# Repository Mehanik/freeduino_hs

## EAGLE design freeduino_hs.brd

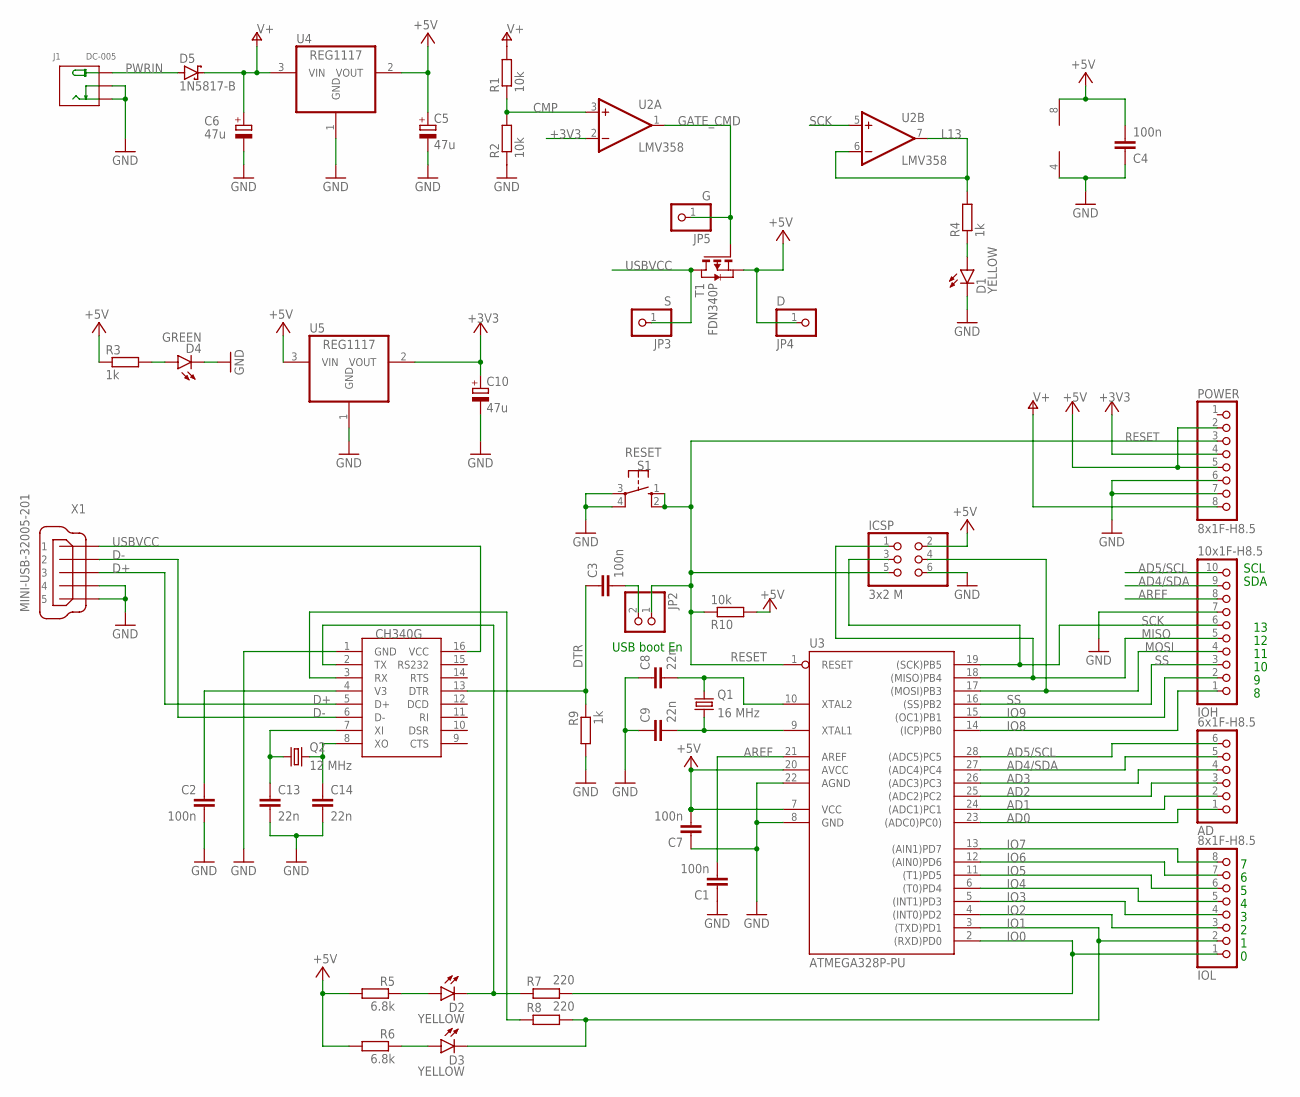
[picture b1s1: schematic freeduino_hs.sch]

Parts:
AD: 6x1F-H8.5; 1X06
C1, C2, C3, C4, C7: 100n; C050-024X044
C5, C6, C10: 47u; E2,5-5
C8, C9, C13, C14: 22n; C050-024X044
D1, D2, D3: YELLOW; LED3MM
D4: GREEN; LED3MM
D5: 1N5817-B; DO41-7.6
ICSP: 3x2 M; 2X03
IOH: 10x1F-H8.5; 1X10
IOL: 8x1F-H8.5; 1X08
J1: DC-005; DCJ3P-14.2X11.0X9.0MM
JP2: PINHD-1X2; 1X02
JP3: S; 1X01
JP4: D; 1X01
JP5: G; 1X01
POWER: 8x1F-H8.5; 1X08
Q1: 16 MHz; HC49/S
Q2: 12 MHz; HC49/S
R1, R2, R10: 10k; 0204/7
R3, R4, R9: 1k; 0204/7
R5, R6: 6.8k; 0204/7
R7, R8: 220; 0204/7
S1: RESET; B3F-10XX
T1: FDN340P; SOT-23
U1: CH340G; SOIC16
U2: LMV358; SO08
U3: ATMEGA328P-PU; DIL28-3
U4, U5: REG1117; SOT223
X1: MINI-USB-32005-201; 32005-201

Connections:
+3V3: C10.+, POWER.4, U2.2 (-IN), U5.2 (VOUT)
+5V: C4.2, C5.+, C7.2, ICSP.2, JP4.1, POWER.2, POWER.5, R3.1, R5.2, R6.2, R10.2, T1.2 (S), U2.8 (V+), U3.7 (VCC), U3.20 (AVCC), U4.2 (VOUT), U5.3 (VIN)
AD0: AD.1, U3.23 ((ADC0)PC0))
AD1: AD.2, U3.24 ((ADC1)PC1)
AD2: AD.3, U3.25 ((ADC2)PC2)
AD3: AD.4, U3.26 ((ADC3)PC3)
AD4/SDA: AD.5, IOH.9, U3.27 ((ADC4)PC4)
AD5/SCL: AD.6, IOH.10, U3.28 ((ADC5)PC5)
AREF: C1.2, IOH.8, U3.21 (AREF)
CMP: R1.1, R2.2, U2.3 (+IN)
D+: U1.5 (D+), X1.3
D-: U1.6 (D-), X1.2
DTR: C3.1, R9.1, U1.13 (DTR)
GATE_CMD: JP5.1, T1.3 (G), U2.1 (OUT)
GND: C1.1, C2.2, C4.1, C5.-, C6.-, C7.1, C8.1, C9.1, C10.-, C13.2, C14.2, D1.K (C), D4.K (C), ICSP.6, IOH.7, J1.-1 (-), J1.-2 (CDN), POWER.6, POWER.7, R2.1, R9.2, S1.3, S1.4 (P1), U1.1 (GND), U2.4 (V-), U3.8 (GND), U3.22 (AGND), U4.1 (GND), U5.1 (GND), X1.4, X1.5
IO0: IOL.1, R7.2, U3.2 ((RXD)PD0)
IO1: D3.K (C), IOL.2, R8.2, U3.3 ((TXD)PD1)
IO2: IOL.3, U3.4 ((INT0)PD2)
IO3: IOL.4, U3.5 ((INT1)PD3)
IO4: IOL.5, U3.6 ((T0)PD4)
IO5: IOL.6, U3.11 ((T1)PD5)
IO6: IOL.7, U3.12 ((AIN0)PD6)
IO7: IOL.8, U3.13 ((AIN1)PD7)
IO8: IOH.1, U3.14 ((ICP)PB0)
IO9: IOH.2, U3.15 ((OC1)PB1)
L13: R4.2, U2.6 (-IN), U2.7 (OUT)
M8RXD: R8.1, U1.3 (RX)
MISO: ICSP.1, IOH.5, U3.18 ((MISO)PB4)
MOSI: ICSP.4, IOH.4, U3.17 ((MOSI)PB3)
unnamed: D1.A, R4.1
unnamed: C2.1, U1.4 (V3)
unnamed: D4.A, R3.2
unnamed: C3.2, JP2.2
unnamed: D3.A, R6.1
unnamed: D2.A, R5.1
unnamed: D2.K (C), R7.1, U1.2 (TX)
PWRIN: D5.A, J1.+
RESET: ICSP.5, JP2.1, POWER.3, R10.1, S1.1 (S), S1.2 (S1), U3.1 (RESET)
SCK: ICSP.3, IOH.6, U2.5 (+IN), U3.19 ((SCK)PB5)
SS: IOH.3, U3.16 ((SS)PB2)
USBVCC: JP3.1, T1.1 (D), U1.16 (VCC), X1.1
V+: C6.+, D5.C, POWER.8, R1.2, U4.3 (VIN)
XI: C13.1, Q2.2, U1.7 (XI)
XO: C14.1, Q2.1, U1.8 (XO)
XTAL1: C9.2, Q1.1, U3.9 (XTAL1)
XTAL2: C8.2, Q1.2, U3.10 (XTAL2)

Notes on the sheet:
USB boot En
SDA
SCL

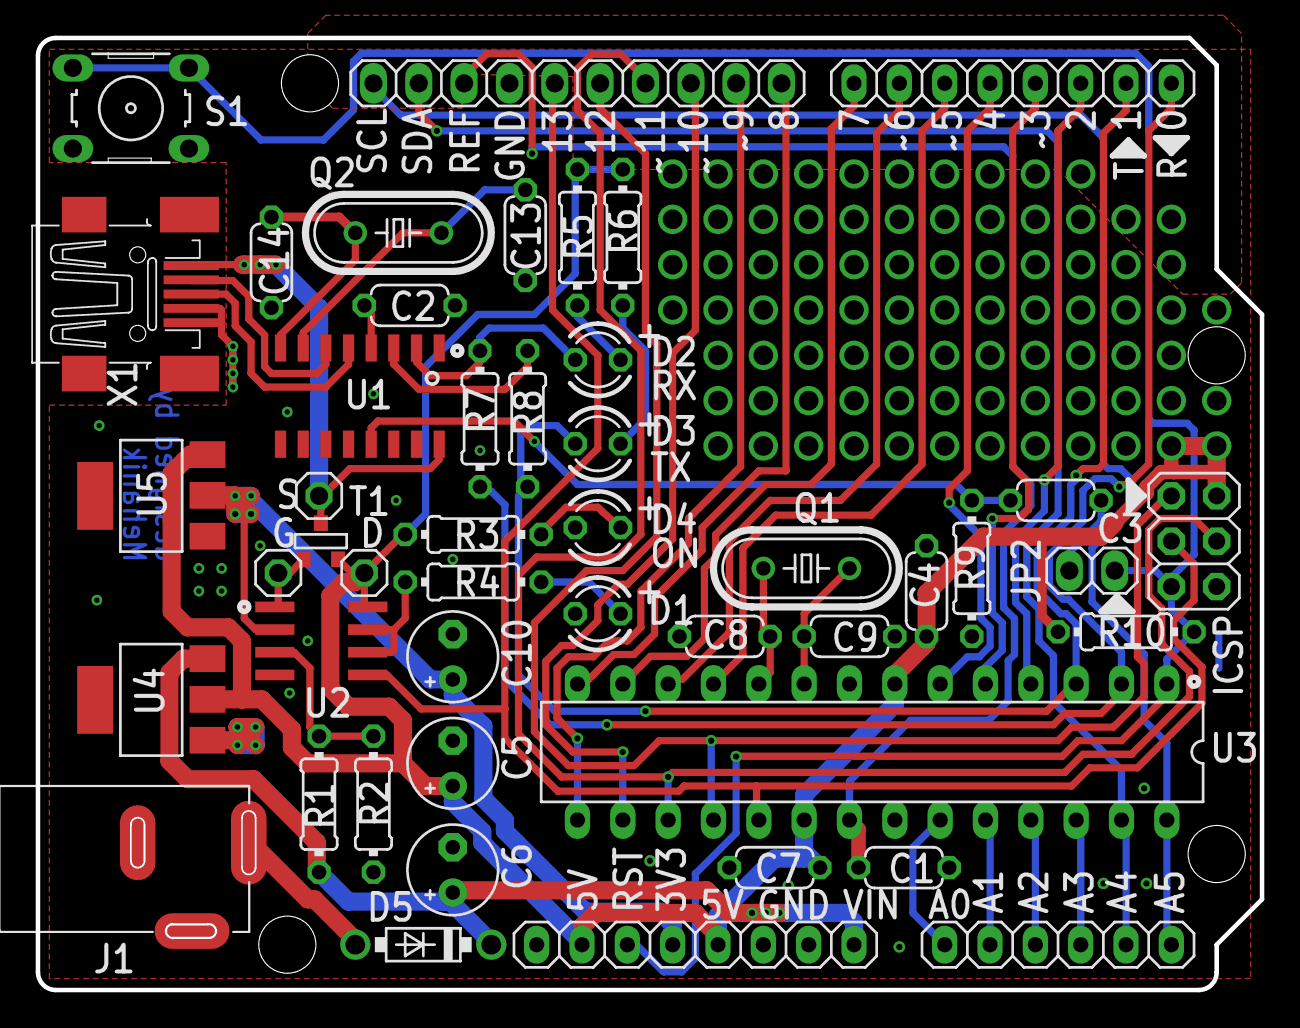
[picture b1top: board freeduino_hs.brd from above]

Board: 2 copper layers, 68.6 x 53.3 mm, 47 parts (0 on the bottom side), 46 nets.

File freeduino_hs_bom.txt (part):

Partlist exported from /home/eugene/eagle/Freeduiono/HS/freeduino_hs.sch at 14.02.17 21:21

Part  Value                Device                        Package               Description                                       MF MPN      OC_FARNELL OC_NEWARK VALUE 
AD    6x1F-H8.5            PINHD-1X6                     1X06                  PIN HEADER                                                                               
C1    100n                 C-EU050-024X044               C050-024X044          CAPACITOR, European symbol                                                               
C2    100n                 C-EU050-024X044               C050-024X044          CAPACITOR, European symbol                                                               
C3    100n                 C-EU050-024X044               C050-024X044          CAPACITOR, European symbol                                                               
C4    100n                 C-EU050-024X044               C050-024X044          CAPACITOR, European symbol                                                               
C5    47u                  CPOL-EUE2.5-5                 E2,5-5                POLARIZED CAPACITOR, European symbol                                                     
C6    47u                  CPOL-EUE2.5-5                 E2,5-5                POLARIZED CAPACITOR, European symbol                                                     
C7    100n                 C-EU050-024X044               C050-024X044          CAPACITOR, European symbol                                                               
C8    22n                  C-EU050-024X044               C050-024X044          CAPACITOR, European symbol                                                               
C9    22n                  C-EU050-024X044               C050-024X044          CAPACITOR, European symbol                                                               
C10   47u                  CPOL-EUE2.5-5                 E2,5-5                POLARIZED CAPACITOR, European symbol                                                     
C13   22n                  C-EU050-024X044               C050-024X044          CAPACITOR, European symbol                                                               
C14   22n                  C-EU050-024X044               C050-024X044          CAPACITOR, European symbol                                                               
D1    YELLOW               LED3MM                        LED3MM                LED                                                                                      
D2    YELLOW               LED3MM                        LED3MM                LED                                                                                      
D3    YELLOW               LED3MM                        LED3MM                LED                                                                                      
D4    GREEN                LED3MM                        LED3MM                LED                                                                                      
D5    1N5817-B             1N5817-B                      DO41-7.6              1.0A SCHOTTKY BARRIER RECTIFIER                                                          
ICSP  3x2 M                PINHD-2X3                     2X03                  PIN HEADER                                                                               
IOH   10x1F-H8.5           PINHD-1X10                    1X10                  PIN HEADER                                                                               
IOL   8x1F-H8.5            PINHD-1X8                     1X08                  PIN HEADER                                                                               
J1    DC-005               CONN-POWER-JACK-2.1MM(DC-005) DCJ3P-14.2X11.0X9.0MM 320120003                                            DC-005                        DC-005
JP2                        PINHD-1X2                     1X02                  PIN HEADER                                                                               
JP3   S                    PINHD-1X1                     1X01                  PIN HEADER                                                                               
JP4   D                    PINHD-1X1                     1X01                  PIN HEADER                                                                               
JP5   G                    PINHD-1X1                     1X01                  PIN HEADER                                                                               
POWER 8x1F-H8.5            PINHD-1X8                     1X08                  PIN HEADER                                                                               
Q1    16 MHz               CRYSTALHC49S                  HC49/S                CRYSTAL                                                       1667008    unknown         
Q2    12 MHz               CRYSTALHC49S                  HC49/S                CRYSTAL                                                       1667008    unknown         
R1    10k                  R-EU_0204/7                   0204/7                RESISTOR, European symbol                                                                
R2    10k                  R-EU_0204/7                   0204/7                RESISTOR, European symbol                                                                
R3    1k                   R-EU_0204/7                   0204/7                RESISTOR, European symbol                                                                
R4    1k                   R-EU_0204/7                   0204/7                RESISTOR, European symbol                                                                
R5    1k                   R-EU_0204/7                   0204/7                RESISTOR, European symbol                                                                
R6    1k                   R-EU_0204/7                   0204/7                RESISTOR, European symbol                                                                
R7    1k                   R-EU_0204/7                   0204/7                RESISTOR, European symbol                                                                
R8    1k                   R-EU_0204/7                   0204/7                RESISTOR, European symbol                                                                
R9    1k                   R-EU_0204/7                   0204/7                RESISTOR, European symbol                                                                
RESET TS42031-160R-TR-7260 10-XX                         B3F-10XX              OMRON SWITCH                                         B3F-1000 176432     36M3542         
T1    FDN340P              PMOSSOT23                     SOT-23                MOS FET                                                       unknown    unknown         
U1    CH340G               CH340G                        SOIC16                                                                                                         
U2    LM393D               LM393D                        SO08                  COMPARATOR                                                                               
U3    ATMEGA328P-PU        ATMEGA328P-PU                 DIL28-3               MICROCONTROLLER                                                                          
U4    REG1117              REG1117                       SOT223                800mA and 1A Low Dropout (LDO) Positive Regulator    REG1117  1097566    14P6981         
U5    REG1117              REG1117                       SOT223                800mA and 1A Low Dropout (LDO) Positive Regulator    REG1117  1097566    14P6981         
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
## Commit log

2017-01-15 Some optimizations
2017-02-12 C2 label moved
2017-02-14 Add gerber
2017-02-14 Add PDF schematic and BOM
2017-04-01 Fix TX-RX routing
    Move ISP connector
    Add reset pull-up resistor
2019-03-10 Re-route some traces
2019-03-10 Update gerber files
2019-03-31 Fix reset pull-up
